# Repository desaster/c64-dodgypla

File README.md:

PLA replacement for C64.

Based on the work by skoe:

[https://bitbucket.org/skoe/pla](1)
[http://skoe.de/docs/c64-dissected/pla/c64_pla_dissected_a4ds.pdf](2)

This design uses the Xilinx XC9536XL, which has 5V tolerant inputs essential
for operation with the Commodore 64.

As opposed to skoe's design, the required CASRAM delay is implemented in
Verilog instead of using additional components.

This project includes:

* A Xilinx ISE project written in Verilog for Xilinx XC9536XL
* A KiCad project including a board designed for home etching

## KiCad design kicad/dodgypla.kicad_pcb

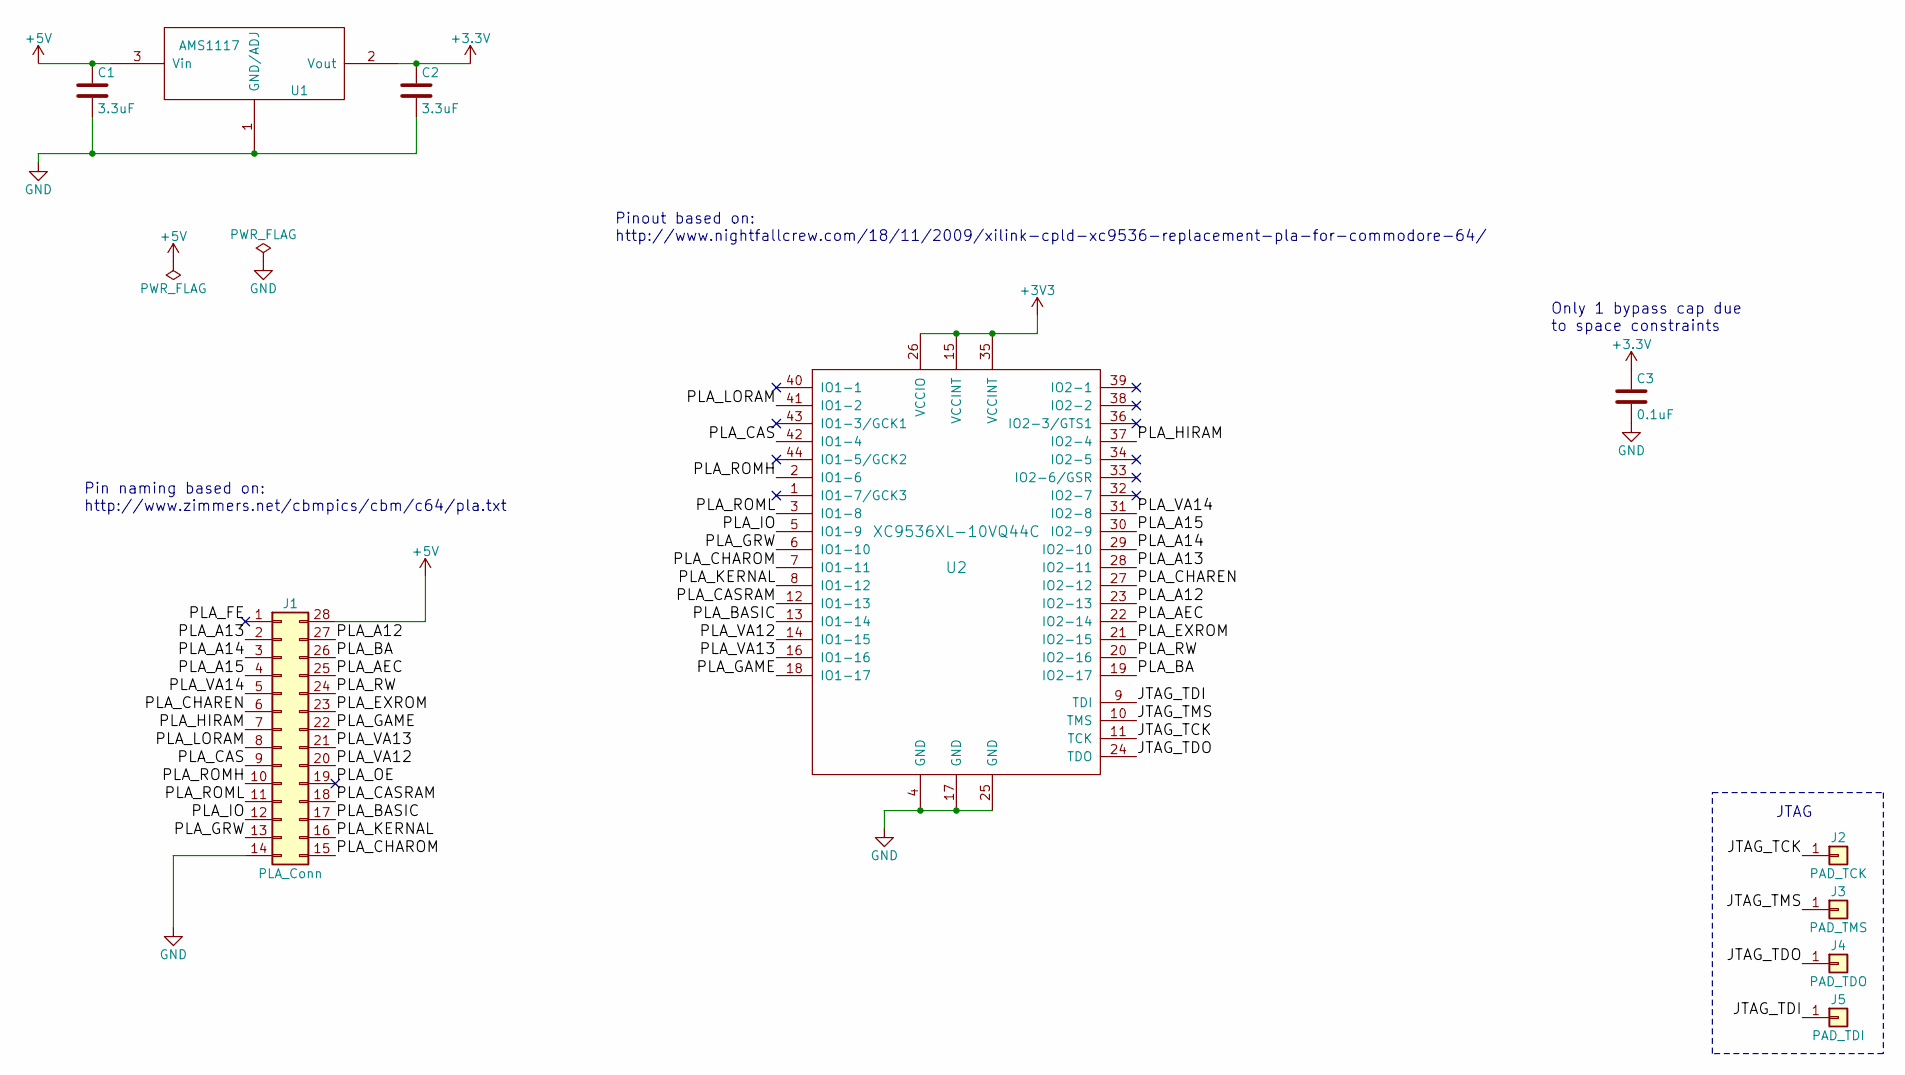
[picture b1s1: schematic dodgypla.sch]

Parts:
C1, C2: 3.3uF; C_0805
C3: 0.1uF; C_0603
J1: PLA_Conn; DIP-28_W15.24mm_Socket
J2: PAD_TCK; testpad_1.6mm
J3: PAD_TMS; testpad_1.6mm
J4: PAD_TDO; testpad_1.6mm
J5: PAD_TDI; testpad_1.6mm
U1: AMS1117; SOT-223-3Lead_TabPin2
U2: XC9536XL-10VQ44C; LQFP-44_10x10mm_Pitch0.8mm

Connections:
+5V: C1.1, J1.28, U1.3 (Vin)
/JTAG_TCK: J2.1, U2.11 (TCK)
/JTAG_TDI: J5.1, U2.9 (TDI)
/JTAG_TDO: J4.1, U2.24 (TDO)
/JTAG_TMS: J3.1, U2.10 (TMS)
/PLA_A12: J1.27, U2.23 (IO2-13)
/PLA_A13: J1.2, U2.28 (IO2-11)
/PLA_A14: J1.3, U2.29 (IO2-10)
/PLA_A15: J1.4, U2.30 (IO2-9)
/PLA_AEC: J1.25, U2.22 (IO2-14)
/PLA_BA: J1.26, U2.19 (IO2-17)
/PLA_BASIC: J1.17, U2.13 (IO1-14)
/PLA_CAS: J1.9, U2.42 (IO1-4)
/PLA_CASRAM: J1.18, U2.12 (IO1-13)
/PLA_CHAREN: J1.6, U2.27 (IO2-12)
/PLA_CHAROM: J1.15, U2.7 (IO1-11)
/PLA_EXROM: J1.23, U2.21 (IO2-15)
/PLA_FE: J1.1
/PLA_GAME: J1.22, U2.18 (IO1-17)
/PLA_GRW: J1.13, U2.6 (IO1-10)
/PLA_HIRAM: J1.7, U2.37 (IO2-4)
/PLA_IO: J1.12, U2.5 (IO1-9)
/PLA_KERNAL: J1.16, U2.8 (IO1-12)
/PLA_LORAM: J1.8, U2.41 (IO1-2)
/PLA_OE: J1.19
/PLA_ROMH: J1.10, U2.2 (IO1-6)
/PLA_ROML: J1.11, U2.3 (IO1-8)
/PLA_RW: J1.24, U2.20 (IO2-16)
/PLA_VA12: J1.20, U2.14 (IO1-15)
/PLA_VA13: J1.21, U2.16 (IO1-16)
/PLA_VA14: J1.5, U2.31 (IO2-8)
GND: C1.2, C2.2, C3.2, J1.14, U1.1 (GND/ADJ), U2.4 (GND), U2.17 (GND), U2.25 (GND)

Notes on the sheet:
JTAG
Pin naming based on: http://www.zimmers.net/cbmpics/cbm/c64/pla.txt
Pinout based on: http://www.nightfallcrew.com/18/11/2009/xilink-cpld-xc9536-replacement-pla-for-commodore-64/
Only 1 bypass cap due to space constraints

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
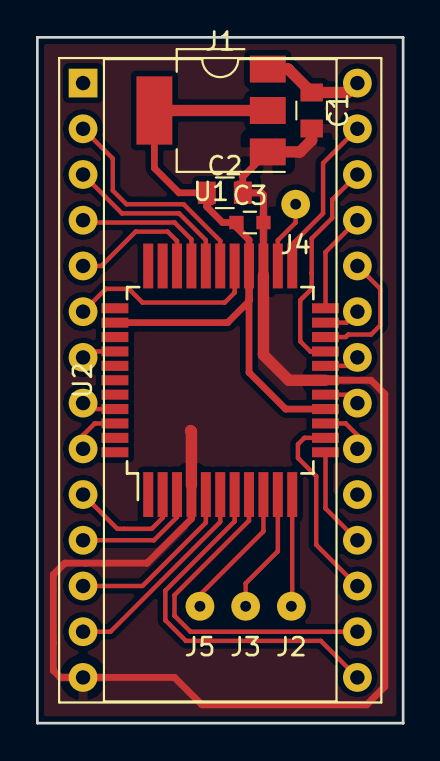
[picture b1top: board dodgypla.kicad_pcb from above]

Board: 2 copper layers, 20.3 x 38.1 mm, 10 parts (0 on the bottom side), 31 nets.

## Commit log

2017-12-12 Basic verilog code implementing the full PLA logic
2017-12-12 Add CASRAM delay and set the slew rate to slow
    These changes should make the verilog code work as a fully functional
    PLA chip on a bare XC9536XL.
2018-01-29 add kicad design
2018-01-29 Add README & LICENSE
2018-01-29 Add schematic in PDF format
2018-01-29 Add .gitignore
2018-01-29 resize image
2018-01-29 Remove extra file
